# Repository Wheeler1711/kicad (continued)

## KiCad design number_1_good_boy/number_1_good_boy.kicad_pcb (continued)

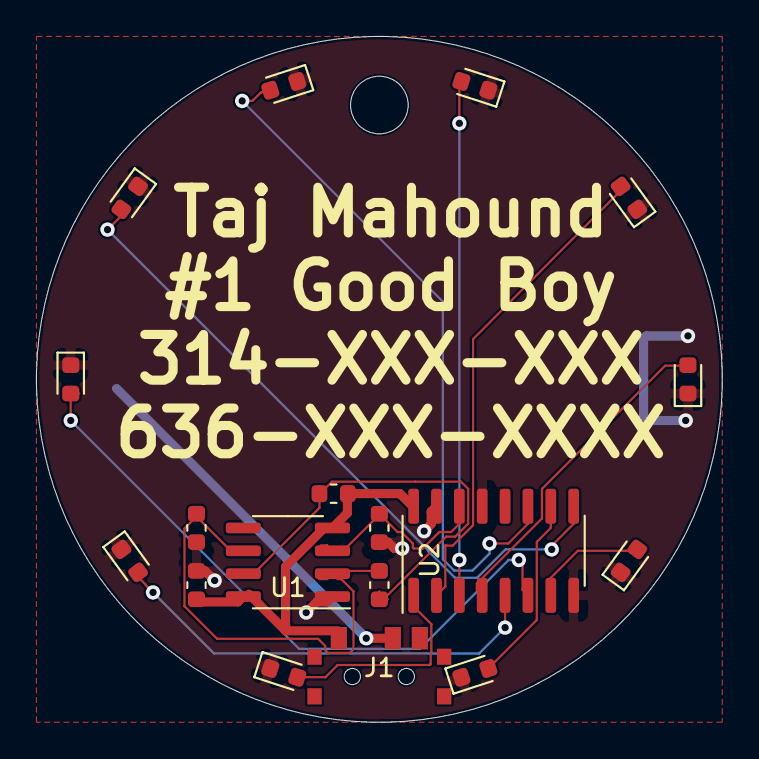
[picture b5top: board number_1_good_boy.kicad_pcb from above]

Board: 2 copper layers, 38.1 x 38.1 mm, 19 parts (1 on the bottom side), 16 nets.

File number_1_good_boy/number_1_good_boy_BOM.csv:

Comment,Designator,Footprint,LCSC
"Battery_Cell","BT1","Battery:BatteryHolder_Keystone_1058_1x2032",""
"CAP 0.01uF","C1","Capacitor_SMD:C_0603_1608Metric","C57112"
"C 10uF","C2","Capacitor_SMD:C_0603_1608Metric"," C19702"
"LED","D1,D2,D3,D4,D5,D6,D7,D8,D9,D10","LED_SMD:LED_0603_1608Metric","C158100"
"XLR3_Switched","J1","switch:surface_mount_switch_SK-3296S-01-L2","C500051"
"R 2.2K","R1","Resistor_SMD:R_0603_1608Metric","C4190"
"R 10K","R2,R3","Resistor_SMD:R_0603_1608Metric","C25804"
"NE555","U1","Package_SO:SOIC-8_3.9x4.9mm_P1.27mm","C7593"
"4017","U2","Package_SO:SOIC-16_3.9x9.9mm_P1.27mm","C11349"

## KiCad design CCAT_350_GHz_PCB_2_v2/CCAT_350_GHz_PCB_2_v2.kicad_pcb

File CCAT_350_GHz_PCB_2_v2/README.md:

## PCB file for interface to 350 GHz CCAT arrays

https://github.com/Wheeler1711/kicad/blob/main/CCAT_350_GHz_PCB_2_v2/Screenshot.png

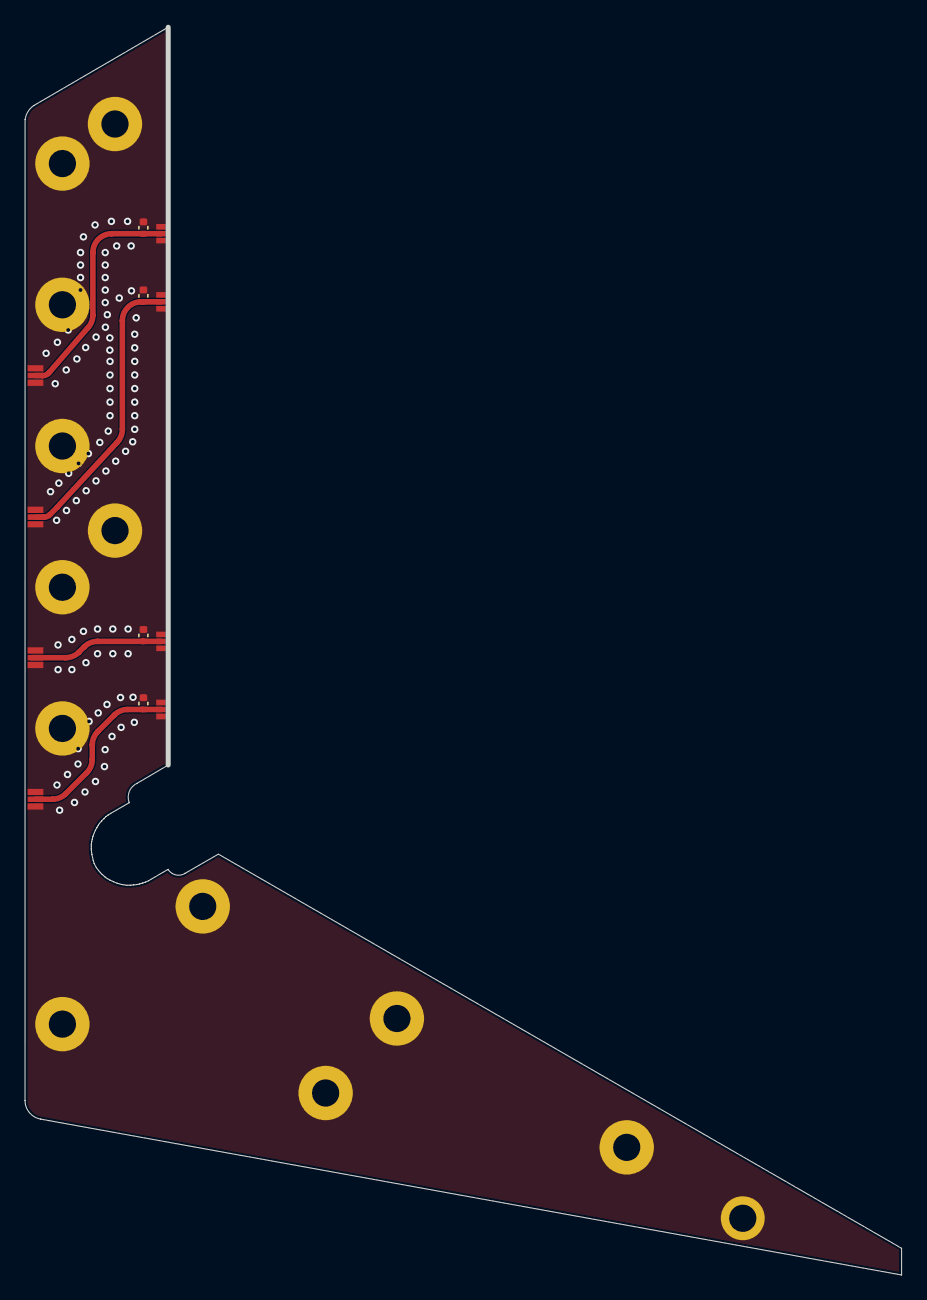
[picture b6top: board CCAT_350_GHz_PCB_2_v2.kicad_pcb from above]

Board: 2 copper layers, 70.6 x 100.8 mm, 12 parts (0 on the bottom side), 5 nets.

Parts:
C1, C2, C3, C4: C; C_0402_1005Metric
J1, J2, J3, J4: Conn_Coaxial; cpw_18_trace_4_gap_rogers_4350B_20_mil_thick
J5, J6, J7, J8: Conn_Coaxial; coax_solder_cpw_18_trace_4_gap_rogers4350B_20_mil_thick

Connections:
GND: C1.2, C2.2, C3.2, C4.2, J1.2 (Ext), J2.2 (Ext), J3.2 (Ext), J4.2 (Ext), J5.2 (Ext), J6.2 (Ext), J7.2 (Ext), J8.2 (Ext)
unnamed: C1.1, J1.1 (In), J5.1 (In)
unnamed: C2.1, J2.1 (In), J6.1 (In)
unnamed: C3.1, J3.1 (In), J7.1 (In)
unnamed: C4.1, J4.1 (In), J8.1 (In)

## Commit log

2021-02-20 initial commit of number 1 goodboy project
    Taj Mahound is the number 1 good boy
    best doggo ever!
2021-02-20 adding in my custom footprints
2021-02-20 Create README.md
    adding in readme to describe how to edit and have made a number 1 good doggo tag
2021-02-20 add a demonstration gif
2021-02-20 Updated readme to display gif of the final product
    update readme with gif of the tag in action
2021-02-20 adding in detail
    adding in detail instructions
2021-02-20 adding pictures of the number 1 good boy
2021-02-20 more detailing
    more details
2021-02-21 moved images to image file added more images
2021-02-21 More detailing and pictures
2021-02-22 adding in more pictures
2021-02-22 fixed a million typos
2021-02-22 update the Readme file
    Just some cleaning up
2021-02-22 few more updates to the readme
2021-02-22 Wife fixes bad grammar
    and other dumb things that he said...
2021-02-25 fixing statement about extended parts
2022-10-16 add *backups to git ignore
2022-10-16 add new board in kicad 6
2022-10-16 modified for different corner feedlines
2022-10-16 add fabrication files and screenshot
2022-11-03 adding in shield for between led mapper and arduino mega
2022-11-03 adding screenshot
2023-10-03 adding pcb for making bias T launches
2023-11-11 adding in led mapper pcb
    also edit git ignore file
2024-02-13 some extra info for ordering/ ancillary parts
2025-02-12 adding in PCB for CCAT 350 GHz arrays
2025-02-12 Update README.md
    fix screenshot
2025-07-02 adding in 25 micro-D breakout
2025-07-02 forgot the README
2025-07-02 typo in README
